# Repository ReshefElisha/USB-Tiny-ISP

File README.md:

# USB-Tiny-ISP
USB ISP programmer using ATTINY45

Modified from design by Ryan and Luke McBee

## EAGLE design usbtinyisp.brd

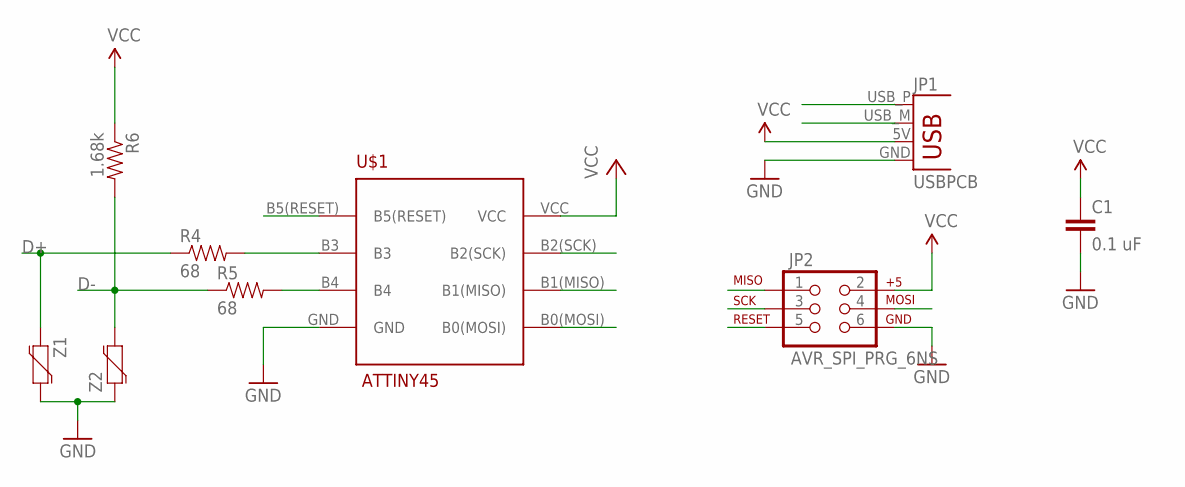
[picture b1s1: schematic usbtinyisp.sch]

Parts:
C1: 0.1 uF; 0603-CAP
JP1: USBPCB; USB-A-PCB
JP2: AVR_SPI_PRG_6NS; 2X3-NS
R4, R5: 68; 0603-RES
R6: 1.68k; 0603-RES
U$1: ATTINY45
Z1, Z2: VARISTOR-0603; 0603-RES

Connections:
D+: JP1.USB_P (D+), R4.1, Z1.1
D-: JP1.USB_M (D-), R5.1, R6.2, Z2.2
GND: C1.2, JP1.GND, JP2.6, U$1.GND, Z1.2, Z2.1
MISO: JP2.1, U$1.B1(MISO)
MOSI: JP2.4, U$1.B0(MOSI)
unnamed: R4.2, U$1.B3
unnamed: R5.2, U$1.B4
RST: JP2.5, U$1.B5(RESET)
SCK: JP2.3, U$1.B2(SCK)
VCC: C1.1, JP1.5V (VBUS), JP2.2, R6.1, U$1.VCC

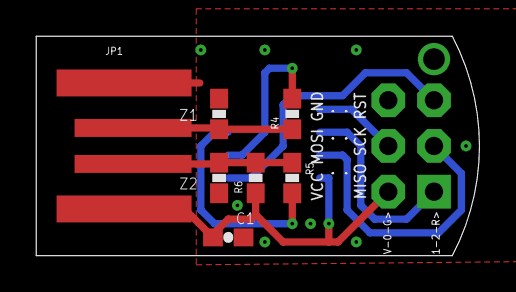
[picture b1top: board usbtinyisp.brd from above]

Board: 2 copper layers, 24.6 x 12.2 mm, 9 parts (1 on the bottom side), 10 nets.

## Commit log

2016-10-30 minified design, created repository
2016-10-31 fixed outline
2016-10-31 via/pours fix
2016-11-01 Silk Screen
2016-11-02 silk screen beautification
2016-11-02 release01

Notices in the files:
parts and their libraries:
SparkFun-Capacitors: Licensing: Creative Commons ShareAlike 4.0 International - https://creativecommons.org/licenses/by-sa/4.0
